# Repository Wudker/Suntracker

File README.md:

# Suntracker – Solar-Tracking Powerbank with MPPT

Suntracker is a design-stage solar-tracking powerbank developed as a mechatronic student project. It combines dual-axis panel positioning, Li-Ion battery charging, powerbank functionality and a simplified P&O-based MPPT concept. Photoresistors guide the automatic search for the optimal panel position, while the INA219 monitors photovoltaic voltage and current. An STM32 microcontroller controls the positioning mechanism, power rails and charging current through a digital potentiometer. The repository contains firmware, PCB and mechanical files, simulations, a BOM, documentation and validation calculations.

## Technologies

`STM32L051C8` `C/C++` `Photovoltaics` `P&O MPPT` `INA219` `MCP40xx` `TP4056` `XL4015` `DRV8833` `Li-Ion battery` `KiCad` `LTspice` `3D printing`

## Usage and development status

After assembling the device, program the microcontroller using an ST-Link and verify the battery polarity, charging current and mechanical movement limits before operation. The controller searches for the strongest light direction, positions the panel and adjusts the charging current according to the measured photovoltaic power. The project is currently a complete design and documentation package supported by approximate mechanical and energy calculations. The next step is to build a physical prototype and verify tracking efficiency, energy balance and long-term outdoor reliability.

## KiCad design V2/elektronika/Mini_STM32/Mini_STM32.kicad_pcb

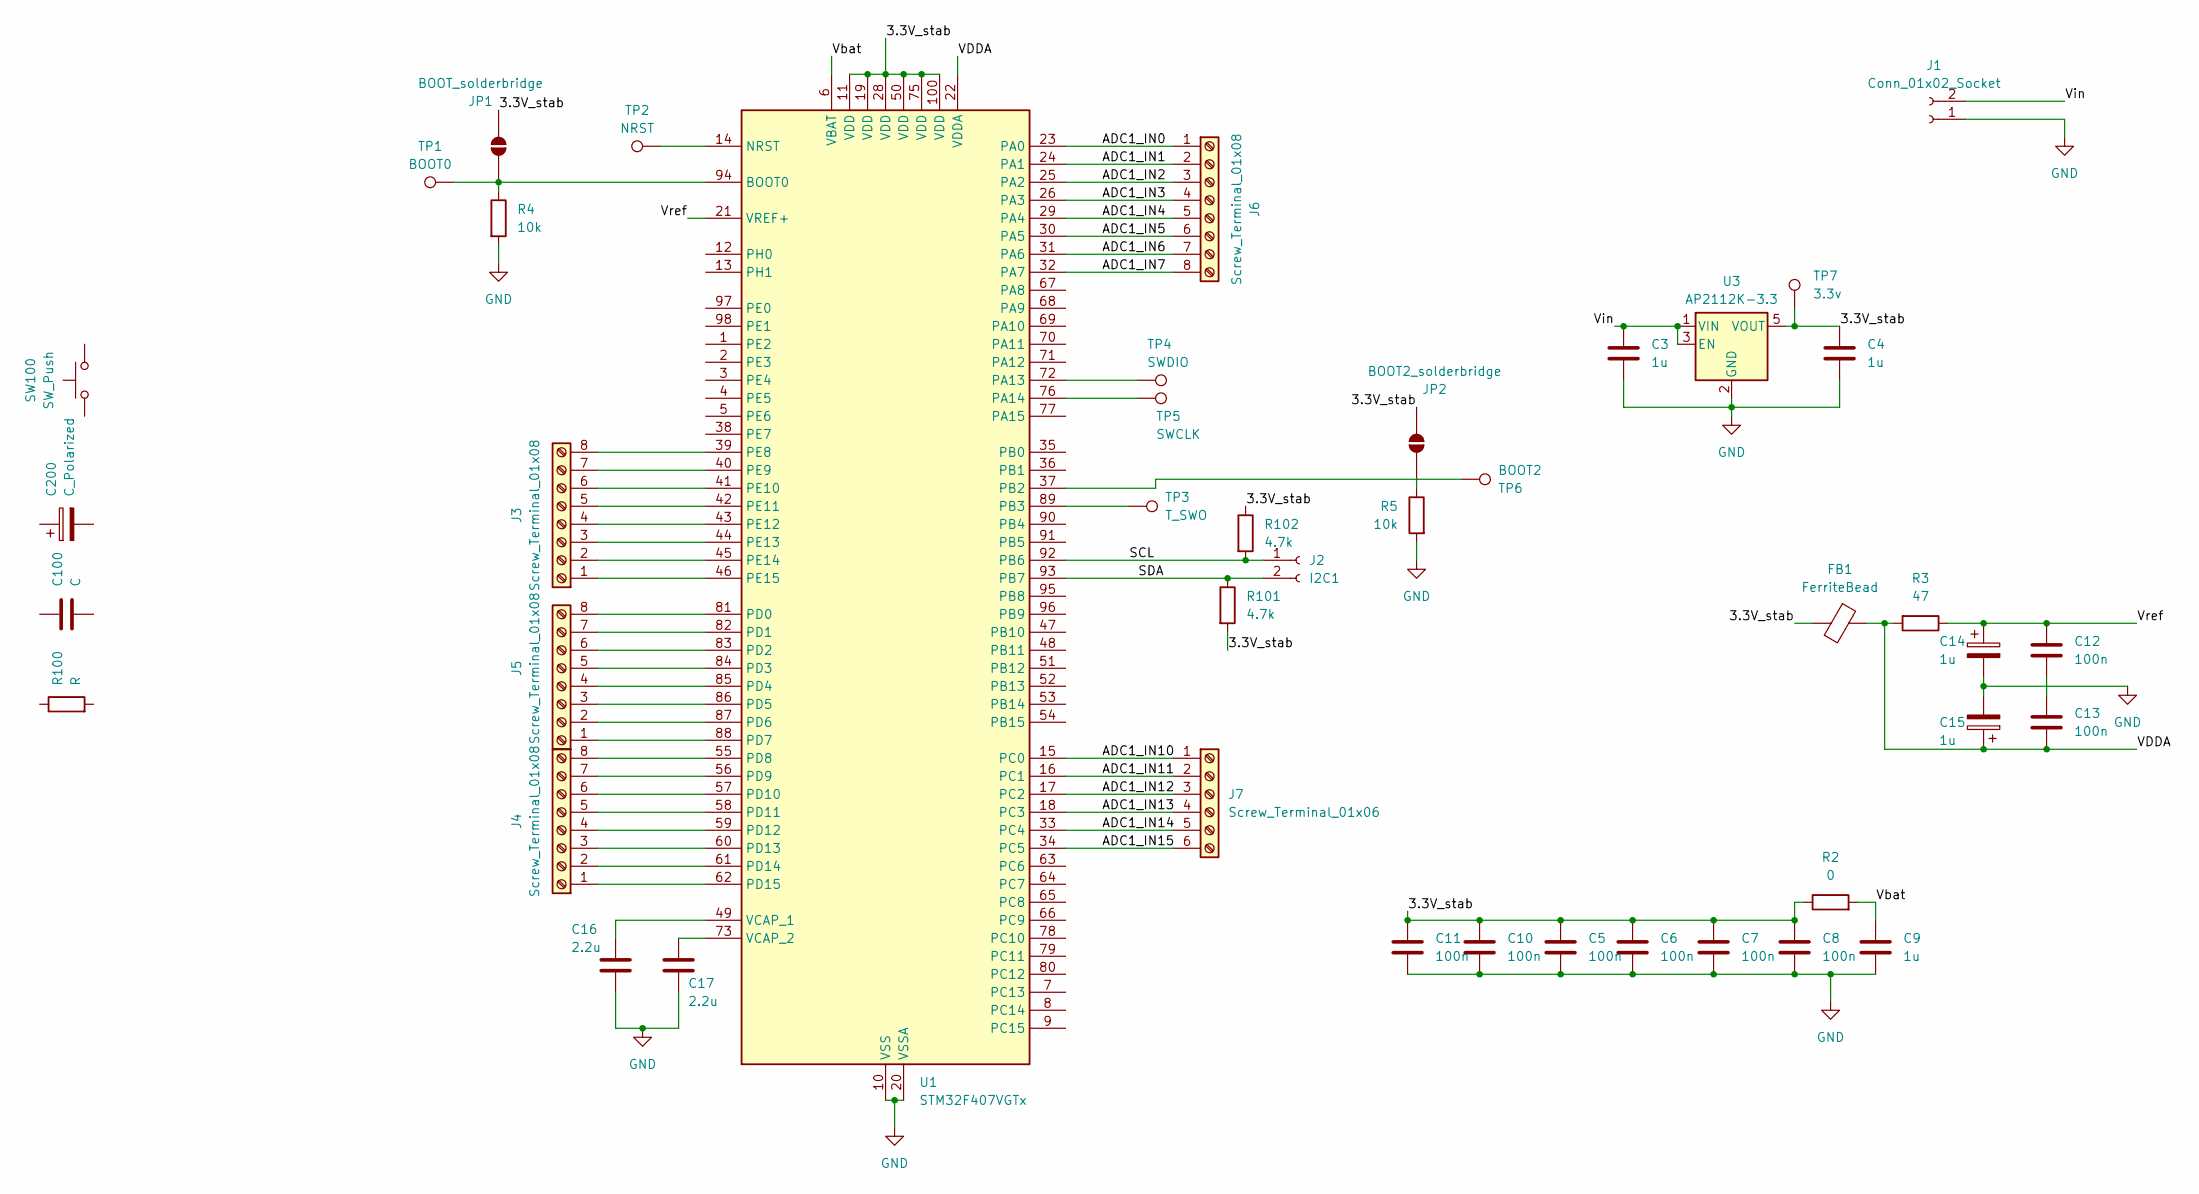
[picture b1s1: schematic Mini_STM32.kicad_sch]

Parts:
C3, C4, C9, C14, C15: 1u; C_1206_3216Metric_Pad1.33x1.80mm_HandSolder
C5, C6, C7, C8, C10, C11, C12, C13: 100n; C_1206_3216Metric_Pad1.33x1.80mm_HandSolder
C16, C17: 2.2u; C_1206_3216Metric_Pad1.33x1.80mm_HandSolder
C100: C
C200: C_Polarized
FB1: FerriteBead; L_1206_3216Metric_Pad1.22x1.90mm_HandSolder
J1: Conn_01x02_Socket; Molex_KK-254_AE-6410-02A_1x02_P2.54mm_Vertical
J2: I2C1; Molex_KK-254_AE-6410-02A_1x02_P2.54mm_Vertical
J3, J4, J5, J6: Screw_Terminal_01x08; TerminalBlock_MaiXu_MX126-5.0-08P_1x08_P5.00mm
J7: Screw_Terminal_01x06; TerminalBlock_MaiXu_MX126-5.0-08P_1x08_P5.00mm
JP1: BOOT_solderbridge; SolderJumper-2_P1.3mm_Open_RoundedPad1.0x1.5mm
JP2: BOOT2_solderbridge; SolderJumper-2_P1.3mm_Open_RoundedPad1.0x1.5mm
R2: 0; R_1206_3216Metric
R3: 47; R_1206_3216Metric
R4, R5: 10k; R_1206_3216Metric
R100: R
R101, R102: 4.7k; R_1206_3216Metric
SW100: SW_Push
TP1: BOOT0; Pin_D1.0mm_L10.0mm
TP2: NRST; Pin_D1.0mm_L10.0mm
TP3: T_SWO; Pin_D1.0mm_L10.0mm
TP4: SWDIO; Pin_D1.0mm_L10.0mm
TP5: SWCLK; Pin_D1.0mm_L10.0mm
TP6: BOOT2; Pin_D1.0mm_L10.0mm
TP7: 3.3v; Pin_D1.0mm_L10.0mm
U1: STM32F407VGTx; LQFP-100_14x14mm_P0.5mm
U3: AP2112K-3.3; SOT-23-5

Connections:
/3.3V_stab: C4.1, C5.1, C6.1, C7.1, C8.1, C10.1, C11.1, FB1.2, JP1.2 (B), JP2.2 (B), R2.1, R101.2, R102.1, TP7.1 (1_1), U1.11 (VDD), U1.19 (VDD), U1.28 (VDD), U1.50 (VDD), U1.75 (VDD), U1.100 (VDD), U3.5 (VOUT)
/ADC1_IN0: J6.1, U1.23 (PA0)
/ADC1_IN1: J6.2, U1.24 (PA1)
/ADC1_IN2: J6.3, U1.25 (PA2)
/ADC1_IN3: J6.4, U1.26 (PA3)
/ADC1_IN4: J6.5, U1.29 (PA4)
/ADC1_IN5: J6.6, U1.30 (PA5)
/ADC1_IN6: J6.7, U1.31 (PA6)
/ADC1_IN7: J6.8, U1.32 (PA7)
/ADC1_IN10: J7.1, U1.15 (PC0)
/ADC1_IN11: J7.2, U1.16 (PC1)
/ADC1_IN12: J7.3, U1.17 (PC2)
/ADC1_IN13: J7.4, U1.18 (PC3)
/ADC1_IN14: J7.5, U1.33 (PC4)
/ADC1_IN15: J7.6, U1.34 (PC5)
/SCL: J2.1, R102.2, U1.92 (PB6)
/SDA: J2.2, R101.1, U1.93 (PB7)
/VDDA: C13.2, C15.1, FB1.1, R3.2, U1.22 (VDDA)
/Vbat: C9.1, R2.2, U1.6 (VBAT)
/Vin: C3.1, J1.2, U3.1 (VIN), U3.3 (EN)
/Vref: C12.1, C14.1, R3.1, U1.21 (VREF+)
GND: C3.2, C4.2, C5.2, C6.2, C7.2, C8.2, C9.2, C10.2, C11.2, C14.2, C15.2, C16.2, C17.2, J1.1, R4.2, R5.2, U1.10 (VSS), U1.20 (VSSA), U1.27 (VSS), U1.74 (VSS), U1.99 (VSS), U3.2 (GND)
unnamed: C12.2, C13.1
unnamed: J3.1, U1.46 (PE15)
unnamed: J3.2, U1.45 (PE14)
unnamed: J3.3, U1.44 (PE13)
unnamed: J3.4, U1.43 (PE12)
unnamed: J3.5, U1.42 (PE11)
unnamed: J3.6, U1.41 (PE10)
unnamed: J3.7, U1.40 (PE9)
unnamed: J3.8, U1.39 (PE8)
unnamed: J4.1, U1.62 (PD15)
unnamed: J4.2, U1.61 (PD14)
unnamed: J4.3, U1.60 (PD13)
unnamed: J4.4, U1.59 (PD12)
unnamed: J4.5, U1.58 (PD11)
unnamed: J4.6, U1.57 (PD10)
unnamed: J4.7, U1.56 (PD9)
unnamed: J4.8, U1.55 (PD8)
unnamed: J5.1, U1.88 (PD7)
unnamed: J5.2, U1.87 (PD6)
unnamed: J5.3, U1.86 (PD5)
unnamed: J5.4, U1.85 (PD4)
unnamed: J5.5, U1.84 (PD3)
unnamed: J5.6, U1.83 (PD2)
unnamed: J5.7, U1.82 (PD1)
unnamed: J5.8, U1.81 (PD0)
unnamed: JP1.1 (A), R4.1, TP1.1 (1_1), U1.94 (BOOT0)
unnamed: JP2.1 (A), R5.1
unnamed: TP2.1 (1_1), U1.14 (NRST)
unnamed: TP4.1 (1_1), U1.72 (PA13)
unnamed: TP5.1 (1_1), U1.76 (PA14)
unnamed: TP6.1 (1_1), U1.37 (PB2)
unnamed: TP3.1 (1_1), U1.89 (PB3)
unnamed: C16.1, U1.49 (VCAP_1)
unnamed: C17.1, U1.73 (VCAP_2)

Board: 2 copper layers, 40 parts (0 on the bottom side), 56 nets, no tracks yet.

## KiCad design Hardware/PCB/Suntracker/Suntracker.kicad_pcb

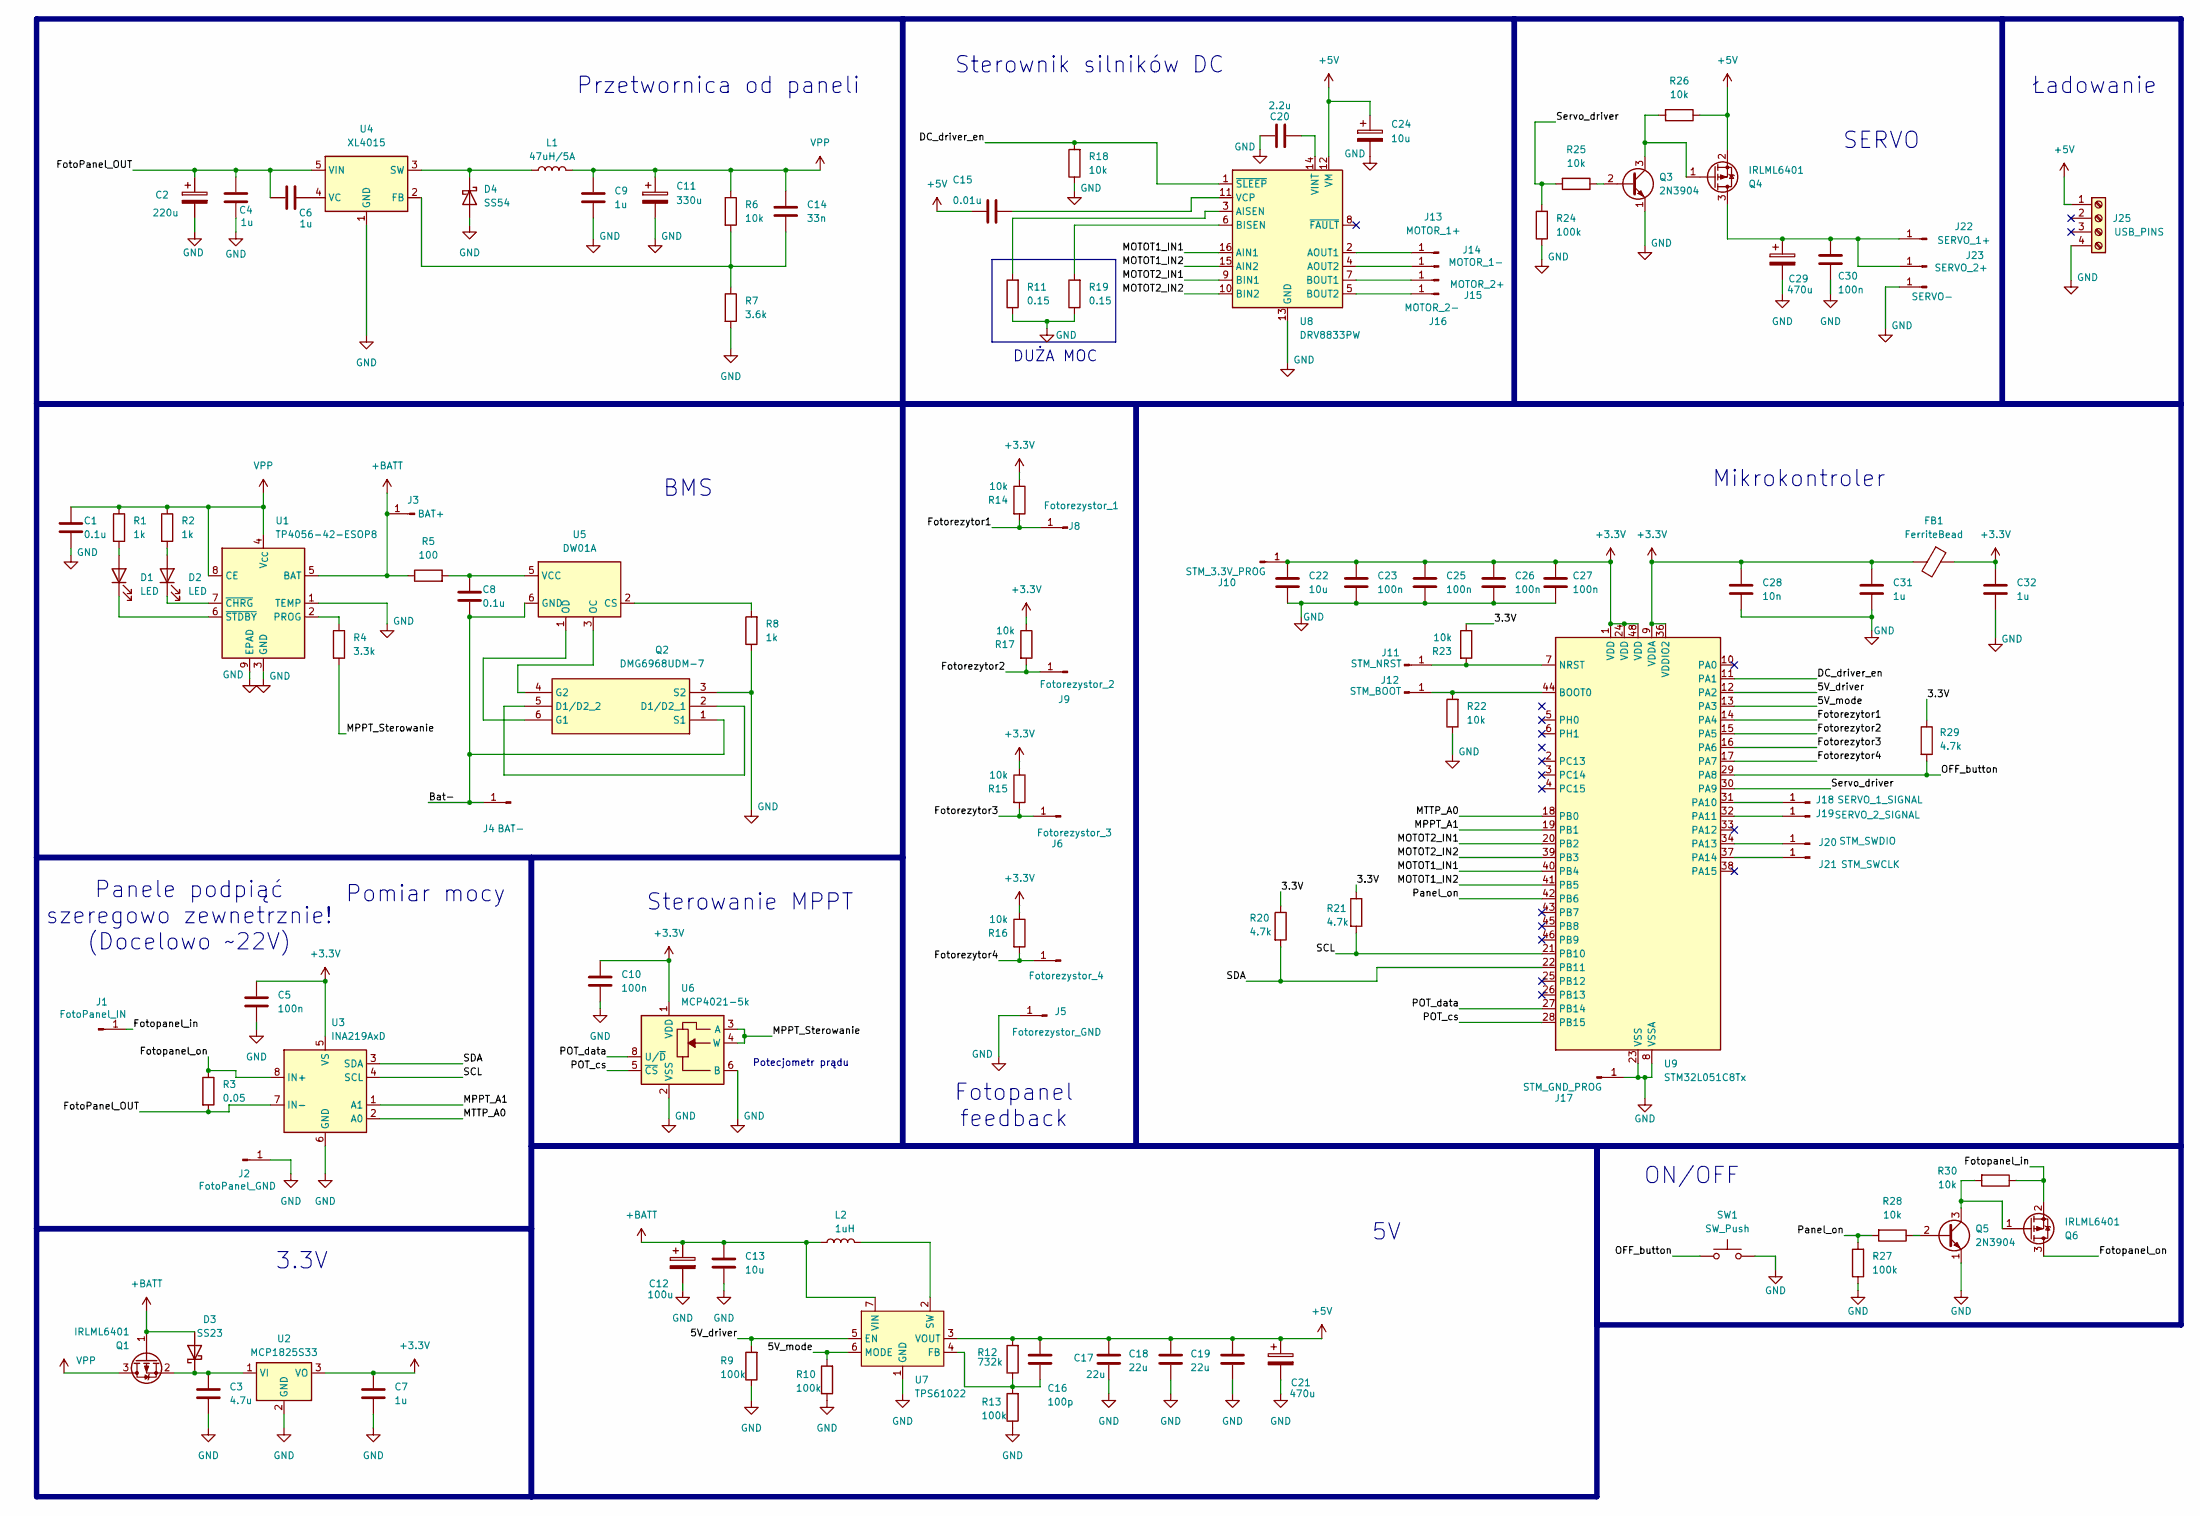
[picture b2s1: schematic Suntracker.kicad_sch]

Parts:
C1, C8: 0.1u; C_1206_3216Metric
C2: 220u; CP_Elec_4x5.8
C3: 4.7u; C_1206_3216Metric
C4, C6, C7, C9, C31, C32: 1u; C_1206_3216Metric
C5, C10, C23, C25, C26, C27, C30: 100n; C_1206_3216Metric
C11: 330u; CP_Elec_4x5.8
C12: 100u; CP_Elec_4x5.8
C13, C22: 10u; C_1206_3216Metric
C14: 33n; C_1206_3216Metric
C15: 0.01u; C_1206_3216Metric
C16: 100p; C_1206_3216Metric
C17, C18, C19: 22u; C_1206_3216Metric
C20: 2.2u; C_1206_3216Metric
C21, C29: 470u; CP_Elec_4x5.8
C24: 10u; CP_Elec_4x5.8
C28: 10n; C_1206_3216Metric
D1, D2: LED; LED_1206_3216Metric
D3: SS23; D_SMA
D4: SS54; D_SMC
FB1: FerriteBead; L_1206_3216Metric
J1: FotoPanel_IN; SolderWire-0.25sqmm_1x01_D0.65mm_OD1.7mm
J2: FotoPanel_GND; SolderWire-0.25sqmm_1x01_D0.65mm_OD1.7mm
J3: BAT+; SolderWire-0.25sqmm_1x01_D0.65mm_OD1.7mm
J4: BAT-; SolderWire-0.25sqmm_1x01_D0.65mm_OD1.7mm
J5: Fotorezystor_GND; SolderWire-0.25sqmm_1x01_D0.65mm_OD1.7mm
J6: Fotorezystor_3; SolderWire-0.25sqmm_1x01_D0.65mm_OD1.7mm
J7: Fotorezystor_4; SolderWire-0.25sqmm_1x01_D0.65mm_OD1.7mm
J8: Fotorezystor_1; SolderWire-0.25sqmm_1x01_D0.65mm_OD1.7mm
J9: Fotorezystor_2; SolderWire-0.25sqmm_1x01_D0.65mm_OD1.7mm
J10: STM_3.3V_PROG; SolderWire-0.25sqmm_1x01_D0.65mm_OD1.7mm
J11: STM_NRST; SolderWire-0.25sqmm_1x01_D0.65mm_OD1.7mm
J12: STM_BOOT; SolderWire-0.25sqmm_1x01_D0.65mm_OD1.7mm
J13: MOTOR_1+; SolderWire-0.25sqmm_1x01_D0.65mm_OD1.7mm
J14: MOTOR_1-; SolderWire-0.25sqmm_1x01_D0.65mm_OD1.7mm
J15: MOTOR_2+; SolderWire-0.25sqmm_1x01_D0.65mm_OD1.7mm
J16: MOTOR_2-; SolderWire-0.25sqmm_1x01_D0.65mm_OD1.7mm
J17: STM_GND_PROG; SolderWire-0.25sqmm_1x01_D0.65mm_OD1.7mm
J18: SERVO_1_SIGNAL; SolderWire-0.25sqmm_1x01_D0.65mm_OD1.7mm
J19: SERVO_2_SIGNAL; SolderWire-0.25sqmm_1x01_D0.65mm_OD1.7mm
J20: STM_SWDIO; SolderWire-0.25sqmm_1x01_D0.65mm_OD1.7mm
J21: STM_SWCLK; SolderWire-0.25sqmm_1x01_D0.65mm_OD1.7mm
J22: SERVO_1+; SolderWire-0.25sqmm_1x01_D0.65mm_OD1.7mm
J23: SERVO_2+; SolderWire-0.25sqmm_1x01_D0.65mm_OD1.7mm
J24: SERVO-; SolderWire-0.25sqmm_1x01_D0.65mm_OD1.7mm
J25: USB_PINS; TerminalBlock_MaiXu_MX126-5.0-04P_1x04_P5.00mm
L1: 47uH/5A; L_12x12mm_H4.5mm
L2: 1uH; L_SXN_SMDRI73
Q1, Q4, Q6: IRLML6401; SOT-23
Q2: DMG6968UDM-7; SOT95P285X140-6N; Manufacturer_Part_Number DMG6968UDM-7
Q3, Q5: 2N3904; TO-92_Inline
R1, R2, R8: 1k; R_1206_3216Metric
R3: 0.05; R_1206_3216Metric
R4: 3.3k; R_1206_3216Metric
R5: 100; R_1206_3216Metric
R6, R14, R15, R16, R17, R18, R22, R23, R25, R26, R28, R30: 10k; R_1206_3216Metric
R7: 3.6k; R_1206_3216Metric
R9, R10, R13, R24, R27: 100k; R_1206_3216Metric
R11, R19: 0.15; R_1206_3216Metric
R12: 732k; R_1206_3216Metric
R20, R21, R29: 4.7k; R_1206_3216Metric
SW1: SW_Push; SW_Push_1P1T_NO_E-Switch_TL3301NxxxxxG
U1: TP4056-42-ESOP8; SOIC-8-1EP_3.9x4.9mm_P1.27mm_EP2.41x3.3mm_ThermalVias
U2: MCP1825S33; SOT-223-3_TabPin2
U3: INA219AxD; SOIC-8_3.9x4.9mm_P1.27mm
U4: XL4015; TO-263-5_TabPin3
U5: DW01A; SOT-23-6
U6: MCP4021-5k; MSOP-8_3x3mm_P0.65mm
U7: TPS61022; Texas_RWU0007A_VQFN-7_2x2mm_P0.5mm
U8: DRV8833PW; TSSOP-16_4.4x5mm_P0.65mm
U9: STM32L051C8Tx; LQFP-48_7x7mm_P0.5mm

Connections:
+3.3V: C5.1, C7.1, C10.1, C22.1, C23.1, C25.1, C26.1, C27.1, C28.1, C31.1, C32.1, FB1.1, FB1.2, J10.1 (Pin_1_1), R14.1, R15.1, R16.1, R17.1, U2.3 (VO), U3.5 (VS), U6.1 (VDD), U9.1 (VDD), U9.9 (VDDA), U9.24 (VDD), U9.36 (VDDIO2), U9.48 (VDD)
+5V: C15.1, C16.2, C17.2, C18.2, C19.2, C21.1, C24.1, J25.1, Q4.2 (S), R12.2, R26.1, U7.3 (VOUT), U8.12 (VM)
+BATT: C12.1, C13.2, D3.2 (A), J3.1 (Pin_1_1), L2.1, Q1.1 (G), R5.1, U1.5 (BAT), U7.7 (VIN)
/3.3V: R20.1, R21.1, R23.1, R29.1
/5V_driver: R9.2, U7.5 (EN), U9.12 (PA2)
/5V_mode: R10.2, U7.6 (MODE), U9.13 (PA3)
/Bat-: C8.2, J4.1 (Pin_1_1), Q2.1 (S1), U5.6 (GND)
/DC_driver_en: R18.2, U8.1 (~SLEEP), U9.11 (PA1)
/FotoPanel_OUT: C2.1, C4.2, C6.1, R3.2, U3.7 (IN-), U4.5 (VIN)
/Fotopanel_in: J1.1 (Pin_1_1), Q6.2 (S), R30.1
/Fotopanel_on: Q6.3 (D), R3.1, U3.8 (IN+)
/Fotorezytor1: J8.1 (Pin_1_1), R14.2, U9.14 (PA4)
/Fotorezytor2: J9.1 (Pin_1_1), R17.2, U9.15 (PA5)
/Fotorezytor3: J6.1 (Pin_1_1), R15.2, U9.16 (PA6)
/Fotorezytor4: J7.1 (Pin_1_1), R16.2, U9.17 (PA7)
/MOTOT1_IN1: U8.16 (AIN1), U9.40 (PB4)
/MOTOT1_IN2: U8.15 (AIN2), U9.41 (PB5)
/MOTOT2_IN1: U8.9 (BIN1), U9.20 (PB2)
/MOTOT2_IN2: U8.10 (BIN2), U9.39 (PB3)
/MPPT_A1: U3.1 (A1), U9.19 (PB1)
/MPPT_Sterowanie: R4.2, U6.3 (A), U6.4 (W)
/MTTP_A0: U3.2 (A0), U9.18 (PB0)
/OFF_button: R29.2, SW1.1, U9.29 (PA8)
/POT_cs: U6.5 (~CS), U9.28 (PB15)
/POT_data: U6.8 (U/~D), U9.27 (PB14)
/Panel_on: R27.2, R28.2, U9.42 (PB6)
/SCL: R21.2, U3.4 (SCL), U9.21 (PB10)
/SDA: R20.2, U3.3 (SDA), U9.22 (PB11)
/Servo_driver: R24.2, R25.2, U9.30 (PA9)
GND: C1.2, C2.2, C3.2, C4.1, C5.2, C7.2, C9.2, C10.2, C11.2, C12.2, C13.1, C17.1, C18.1, C19.1, C20.1, C21.2, C22.2, C23.2, C24.2, C25.2, C26.2, C27.2, C28.2, C29.2, C30.2, C31.2, C32.2, D4.2 (A), J2.1 (Pin_1_1), J5.1 (Pin_1_1), J17.1 (Pin_1_1), J24.1 (Pin_1_1), J25.4, Q2.3 (S2), Q3.1 (E), Q5.1 (E), R7.2, R8.1, R9.1, R10.1, R11.1, R13.1, R18.1, R19.1, R22.1, R24.1, R27.1, SW1.2, U1.1 (TEMP), U1.3 (GND), U1.9 (EPAD), U2.2 (GND), U3.6 (GND), U4.1 (GND), U6.2 (VSS), U6.6 (B), U7.1 (GND), U8.13 (GND), U9.8 (VSSA), U9.23 (VSS), U9.35 (VSS), U9.47 (VSS)
unnamed: D1.2 (A), R1.2
unnamed: D1.1 (K), U1.6 (~STDBY)
unnamed: D2.2 (A), R2.2
unnamed: D2.1 (K), U1.7 (~CHRG)
unnamed: C3.1, D3.1 (K), Q1.2 (S), U2.1 (VI)
unnamed: D4.1 (K), L1.1, U4.3 (SW)
unnamed: J11.1 (Pin_1_1), R23.2, U9.7 (NRST)
unnamed: J12.1 (Pin_1_1), R22.2, U9.44 (BOOT0)
unnamed: J13.1 (Pin_1_1), U8.2 (AOUT1)
unnamed: J14.1 (Pin_1_1), U8.4 (AOUT2)
unnamed: J15.1 (Pin_1_1), U8.7 (BOUT1)
unnamed: J16.1 (Pin_1_1), U8.5 (BOUT2)
unnamed: J18.1 (Pin_1_1), U9.31 (PA10)
unnamed: J19.1 (Pin_1_1), U9.32 (PA11)
unnamed: J20.1 (Pin_1_1), U9.34 (PA13)
unnamed: J21.1 (Pin_1_1), U9.37 (PA14)
unnamed: C29.1, C30.1, J22.1 (Pin_1_1), J23.1 (Pin_1_1), Q4.3 (D)
unnamed: Q2.2 (D1/D2_1), Q2.5 (D1/D2_2)
unnamed: Q2.6 (G1), U5.1 (OD)
unnamed: Q2.4 (G2), U5.3 (OC)
unnamed: Q3.2 (B), R25.1
unnamed: Q3.3 (C), Q4.1 (G), R26.2
unnamed: Q5.2 (B), R28.1
unnamed: Q5.3 (C), Q6.1 (G), R30.2
unnamed: R4.1, U1.2 (PROG)
unnamed: C14.2, R6.2, R7.1, U4.2 (FB)
unnamed: C6.2, U4.4 (VC)
unnamed: R8.2, U5.2 (CS)
unnamed: C8.1, R5.2, U5.5 (VCC)
unnamed: C16.1, R12.1, R13.2, U7.4 (FB)
unnamed: L2.2, U7.2 (SW)
unnamed: R11.2, U8.3 (AISEN)
unnamed: R19.2, U8.6 (BISEN)
unnamed: C15.2, U8.11 (VCP)
unnamed: C20.2, U8.14 (VINT)
VPP: C1.1, C9.1, C11.1, C14.1, L1.2, Q1.3 (D), R1.1, R2.1, R6.1, U1.4 (V_{CC}), U1.8 (CE)

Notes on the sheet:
DUŻA MOC
Mikrokontroler
Fotopanel feedback
ON/OFF
Sterownik silników DC
Sterowanie MPPT
3.3V
Przetwornica od paneli
BMS
Pomiar mocy
Panele podpiąć szeregowo zewnetrznie! (Docelowo ~22V)
Potecjometr prądu
SERVO
Ładowanie

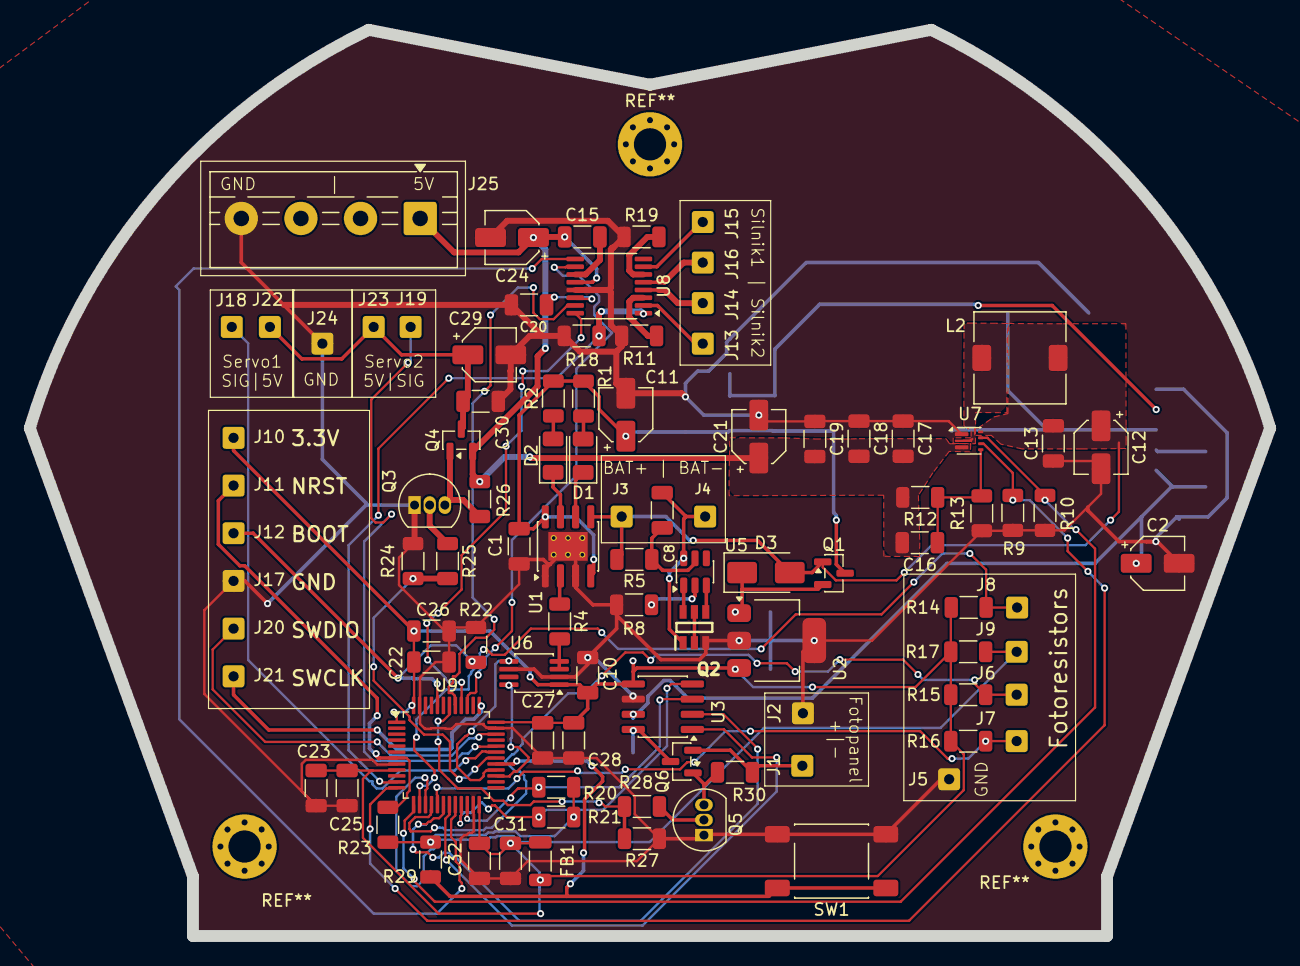
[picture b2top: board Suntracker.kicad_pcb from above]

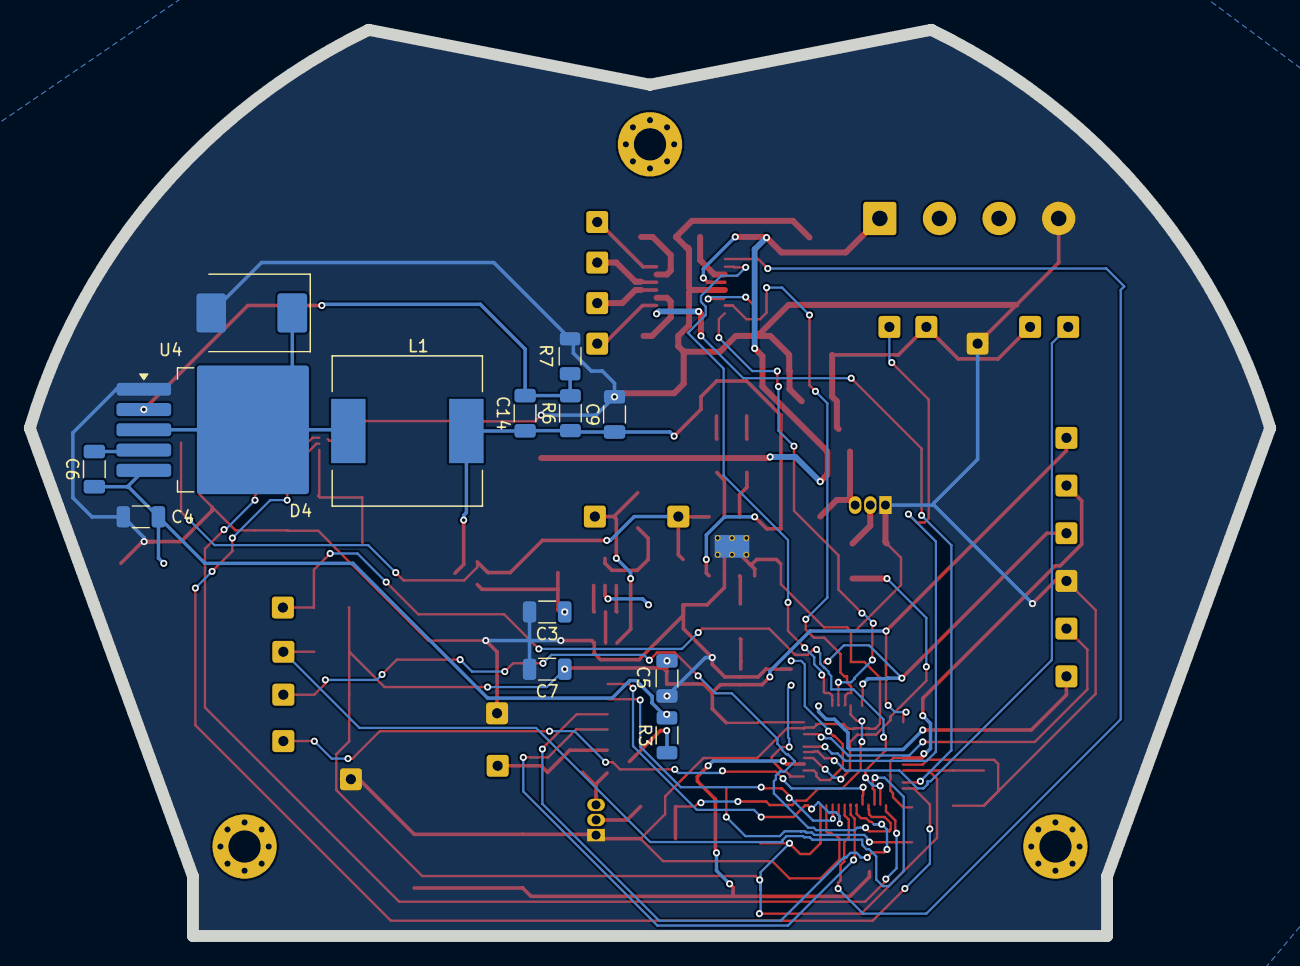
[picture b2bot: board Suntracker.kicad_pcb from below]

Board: 2 copper layers, 104.0 x 76.0 mm, 110 parts (13 on the bottom side), 66 nets.

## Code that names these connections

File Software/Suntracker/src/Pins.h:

#pragma once
#include <Arduino.h>

// Digital potentiometer
const uint16_t POT_data = PB14;
const uint16_t POT_cs = PB15;

// MPPT analog inputs
const uint16_t MPPT_A0 = PB0;
const uint16_t MPPT_A1 = PB1;

// Photorezistors - ADC
const uint16_t Photorezistor_1 = PA4;
const uint16_t Photorezistor_2 = PA5;
const uint16_t Photorezistor_3 = PA6;
const uint16_t Photorezistor_4 = PA7;

// Motor control pins
const uint16_t Motor1_in1 = PB4;
const uint16_t Motor1_in2 = PB5;

const uint16_t Motor2_in1 = PB2;
const uint16_t Motor2_in2 = PB3;

// Servo
const uint16_t Servo_power_enable = PA9;
const uint16_t Servo_signal = PA10;
const uint16_t Servo_2_signal = PA11;

// Power control pins
const uint16_t Motor_driver_enable = PA1;
const uint16_t Logic_5V_enable = PA2;
const uint16_t Logic_5V_mode = PA3;
const uint16_t Panel_enable = PB6;

// Button
const uint16_t POWER_ON = PA8; 

// I2C
const uint32_t PIN_I2C_SCL = PB10;
const uint32_t PIN_I2C_SDA = PB11;

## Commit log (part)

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2026-06-01 Add Inventor simulation images and video
    Add visual assets for the Inventor simulation: five PNG frames (kolizja_1.png, kolizja_2.png, kolizja_3-1.png, kolizja_3-2.png, kolizja_4.png) and a sequence video (sequence.avi) under Simulations/In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
2026-06-01 Add Harvest_Update and main state machine
    Introduce a Harvest_Update routine and a simple state machine to manage startup, harvesting, folding and sleep cycles.
    Changes:
    - Include Photorezistors.h.
    - Update System_Start to find/set an optimal panel position before initializing MPPT.
    - Add Harvest_Update() which powers the panel, finds optimal position and starts MPPT.
    - Modify System_Sleep() to disable 5V logic power instead of directly toggling panel power.
2026-06-01 Remove System_Init and fix System_Fold call
    Remove the call to System_Init() from System_Start() and delete its prototype from General.h, indicating the init routine is no longer used. Also correct a typo in main.cpp by changing system_Fold() 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
2026-06-02 Infer motor direction from sign; update callers
    Refactor motor API to remove explicit direction boolean: Set_Motor1_Direction and Set_Motor2_Direction now take a signed float (angle/distance) and determine direction from the sign. Updated function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
2026-06-02 Add power-on interrupt and state handler
    Introduce a hardware interrupt for the POWER_ON pin and a corresponding interrupt() routine that wakes the system: when in Sleep it moves to START, otherwise it sets the state to FOLD. attachInterrup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
2026-06-03 Use signed position and refine motor stepping
    Change position type to signed (uint16_t -> int16_t) in General.cpp to allow negative/directional offsets. Add <math.h> include in Motors.cpp. Fix Motors.h parameter order/names to match intended sem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
2026-06-03 Add power state and hardware timer
    Introduce power management and timer-driven harvest updates: make Initial_State volatile, add Power_state enum and Power flag, and add Harvest_time and Timer_counter. Replace generic interrupt() with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
2026-06-03 Add interrupt module and initialization
    Introduce Interrupt.h/cpp to centralize power/state enums, timer and ISRs (PowerButton_ISR, Harvest_Update_interrupt) and initialize hardware interrupts. Add Pinout_init and Wire_Init (General.cpp/h)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
2026-06-03 Add STM32 RTC/LowPower and integrate sleep
    Introduce STM32 low-power and RTC support and integrate it into the system sleep flow. Added STM32LowPower.{h,cpp}, STM32RTC.{cpp,h}, low_power.c/.h and rtc.c/.h (ST licensing headers included) and a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
2026-06-03 Use wake flag for power-button ISR
    Refactor interrupt handling so the ISR only sets a wake flag and deferred handling runs in normal context. Changes include:
    - Include interrupt.h where needed and expose shared symbols.
    - Add volatile Button_wakeup_flag and set it in PowerButton_ISR (no heavy logic in ISR).
    - Add Handle_Power_Button() that performs the previous ISR state transitions (Power/Initial_State/Timer_counter).
    - In System_Sleep(), clear Button_wakeup_flag before sleep, then after deepSleep call Handle_Power_Button() if the flag was set, otherwise call Harvest_Update_interrupt().
    - Move/declare shared timer and state globals (Timer_counter, Initial_State, Power) as externs in Inter
2026-06-03 Move init calls and add wakeup handler
    Move Pinout_init() and Wire_Init() to the start of setup() (before RTC/LowPower init) and adjust brace style. Remove the late Interrupt_Init() call. In loop(), add a Button_wakeup_flag check that dis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
2026-06-03 Disable interrupts when clearing wakeup flag
    In System_Sleep(), clear Button_wakeup_flag inside noInterrupts()/interrupts() to avoid race conditions with interrupt handlers before calling Handle_Power_Button(). This ensures the wakeup flag is r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
2026-06-04 Add datasheets and Suntracker backup
    Add multiple component datasheets and project documentation. This commit adds PDFs for 2N3903, DMG6968UDM, DRV8833, DW01A, INA219, IRLML6401, MCP1825, MG90S, STM32L051X6, TP4056, TPS61022, XL4015, th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
2026-06-04 Refactor interrupt flags & add sunlight safety
    Make ISR routines minimal and expose new flags: replace Button_wakeup_flag with powerButtonFlag and add wakeTickFlag (set in ISR) so the main loop does deferred processing. Move Timer_counter/volatil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
2026-06-04 Use panel voltage threshold for critical sunlight
    Add MIN_PANEL_START_VOLTAGE macro and change sun-tracking logic to decide Critical_Sunlight based on measured panel voltage. Find_optimal_position now clears the flag, reads the average panel voltage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
2026-06-04 Rename Button_wakeup_flag to powerButtonFlag
    Replace uses of Button_wakeup_flag with powerButtonFlag and remove the duplicate volatile declaration. General.cpp now initializes and checks powerButtonFlag (clearing it inside noInterrupts/interrup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
2026-06-04 Make MPPT_Init return status and handle shutdown
    Change MPPT_Init from void to bool and return false when Critical_Sunlight is detected to avoid initializing the MPPT in unsafe conditions. Update MPPT.h prototype and MPPT.cpp (added Interrupt.h and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
2026-06-04 Move RTC and wakeup setup to Interrupts_init
    Centralize RTC and low-power wakeup configuration in a new Interrupts_init() function within Interrupt.cpp and expose rtc as an extern in headers/main. Added Button_wakeup_flag and its extern declara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
2026-06-05 Add CAD hardware parts; update assembly
    Add multiple CAD part files (STEP and IPT) for fasteners and hardware: 92000A013, 92000A017, 92000A113 screws; 94459A110 heat-set inserts; 98886A826 PEEK hex nut; a 6x6 button; plus various OldVersio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
2026-06-05 Update motor speeds; add BOM, models & PCB lock
    Adjust motor speed constants and add project artifacts: Motors.h - change MOTOR1_speed from 120 to 100 RPM and MOTOR2_speed from 120 to 400 RPM. Add BOM/BOM.xlsx and its temp file (~$BOM.xlsx). Repla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
2026-06-05 Cleaning be4 final documentation
2026-06-05 cleaning
2026-06-06 Update BOM spreadsheet and Suntracker PDF
    Replace BOM/BOM.xlsx and Documentation/Suntracker.pdf with updated binary versions. The spreadsheet updates the bill of materials and the PDF refreshes the Suntracker documentation; no source code ch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
2026-06-06 Add simulations and update motor parameters
    Add Inventor and LTspice simulation assets and update motor configuration.
    - Added Simulations/Inventor/README.md and Simulations/Ltspice/README.md describing collision analysis and animation of the PV array end positions.
    - Added Simulations/Ltspice/H_bridge.asc LTspice schematic for an H-bridge/motor drive.
    - Modified Software/Suntracker/src/Motors.h: adjusted MOTOR1_speed (100 -> 83) and MOTOR2_speed (400 -> 342) to reflect proportional speed reduction from 6V to 5V, reduced speed_start from 120 to 100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
2026-06-06 Hotfix od readme
2026-06-14 Final touches
2026-06-14 Finishing touches
